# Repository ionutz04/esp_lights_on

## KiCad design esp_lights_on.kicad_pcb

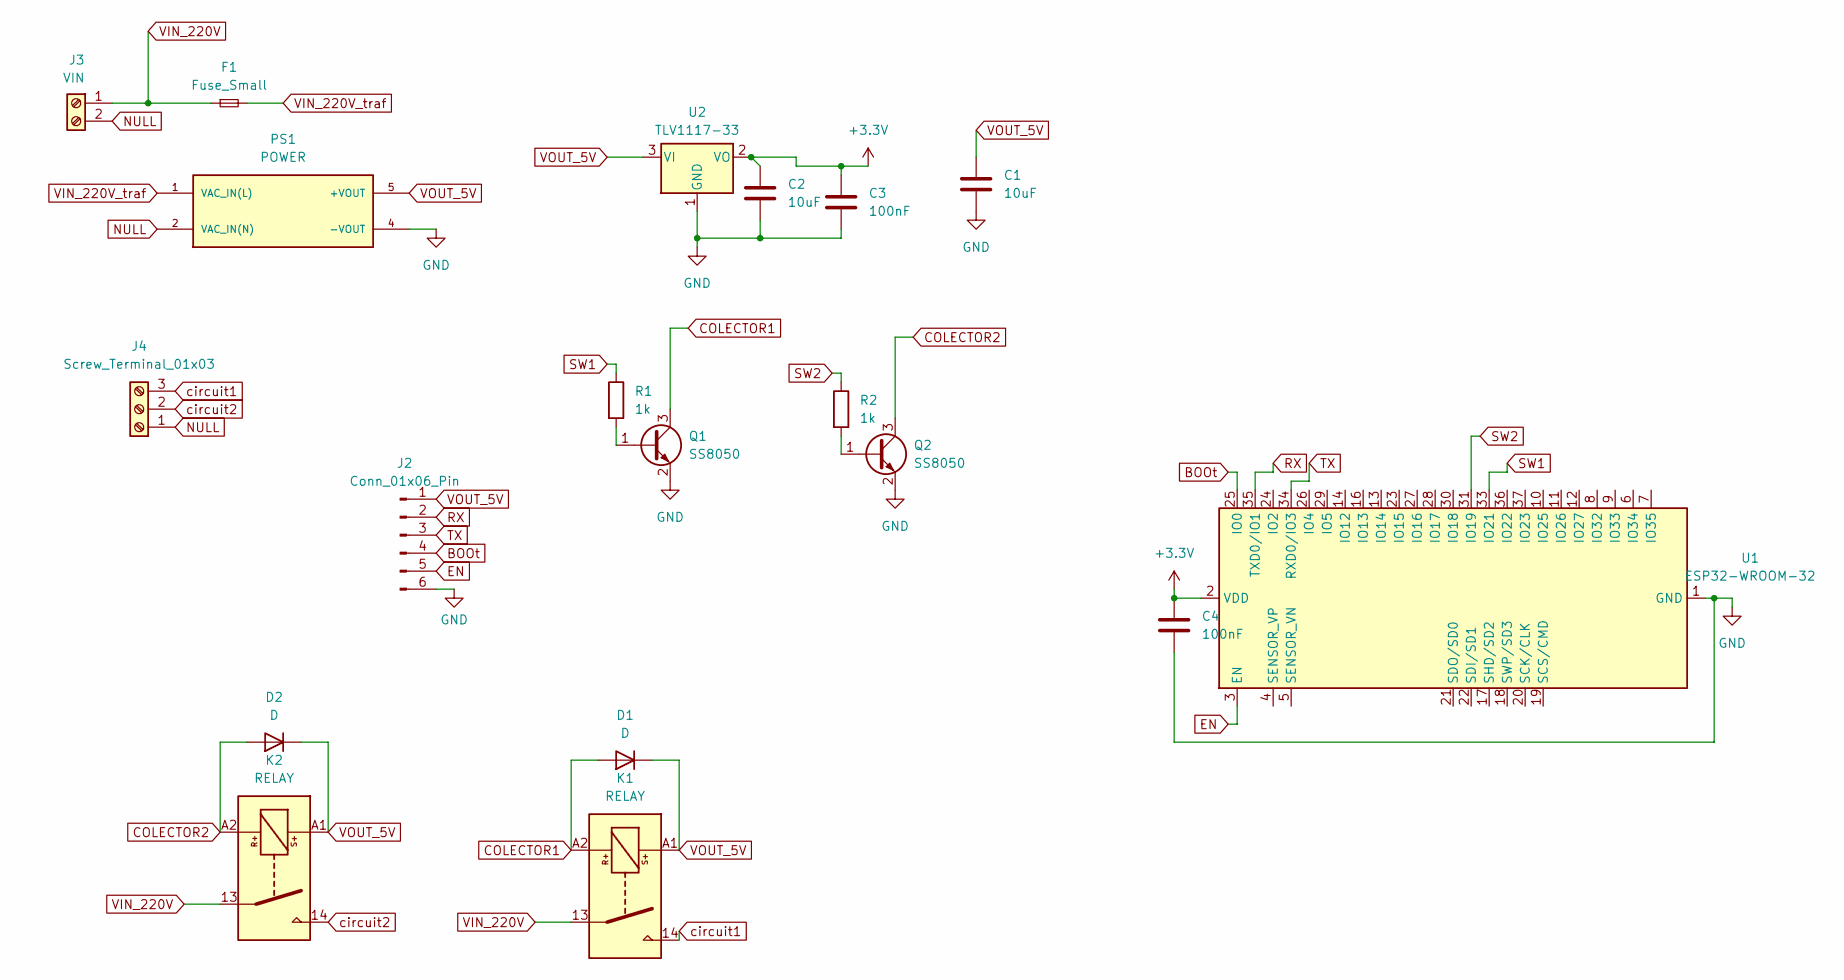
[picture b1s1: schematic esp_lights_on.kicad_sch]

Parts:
C1: 10uF; C_1210_3225Metric_Pad1.33x2.70mm_HandSolder
C2: 10uF; C_0805_2012Metric_Pad1.18x1.45mm_HandSolder
C3, C4: 100nF; C_0805_2012Metric_Pad1.18x1.45mm_HandSolder
D1, D2: D; D_SMA_Handsoldering
F1: Fuse_Small; Fuse_Schurter_UMZ250
J2: Conn_01x06_Pin; PinHeader_1x06_P2.54mm_Vertical
J3: VIN; TerminalBlock_Phoenix_MKDS-1,5-2-5.08_1x02_P5.08mm_Horizont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
J4: Screw_Terminal_01x03; TerminalBlock_Phoenix_MKDS-1,5-3-5.08_1x03_P5.08mm_Horizont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
K1, K2: RELAY; Relay_SPST_Panasonic_ADW11
PS1: POWER; CONV_RACM06E-12SK_277; PARTREV PRELIMINARY
Q1, Q2: SS8050; SOT-23-3
R1, R2: 1k; R_0805_2012Metric
U1: ESP32-WROOM-32
U2: TLV1117-33; SOT-223-3_TabPin2

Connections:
+3.3V: C2.1, C3.1, C4.1, U1.2 (VDD), U2.2 (VO)
BOOt: J2.4, U1.25 (IO0)
COLECTOR1: D1.2 (A), K1.A2, Q1.3 (C)
COLECTOR2: D2.2 (A), K2.A2, Q2.3 (C)
EN: J2.5, U1.3 (EN)
GND: C1.2, C2.2, C3.2, C4.2, J2.6, PS1.4 (-VOUT), Q1.2 (E), Q2.2 (E), U1.1 (GND), U1.15 (GND), U1.38 (GND), U1.39 (GND), U2.1 (GND)
NULL: J3.2, J4.1, PS1.2 (VAC_IN(N))
unnamed: Q1.1 (B), R1.2
unnamed: Q2.1 (B), R2.2
RX: J2.2, U1.35 (TXD0/IO1)
SW1: R1.1, U1.33 (IO21)
SW2: R2.1, U1.31 (IO19)
TX: J2.3, U1.34 (RXD0/IO3)
VIN_220V: F1.1, J3.1, K1.13, K2.13
VIN_220V_traf: F1.2, PS1.1 (VAC_IN(L))
VOUT_5V: C1.1, D1.1 (K), D2.1 (K), J2.1, K1.A1, K2.A1, PS1.5 (+VOUT), U2.3 (VI)
circuit1: J4.3, K1.14
circuit2: J4.2, K2.14

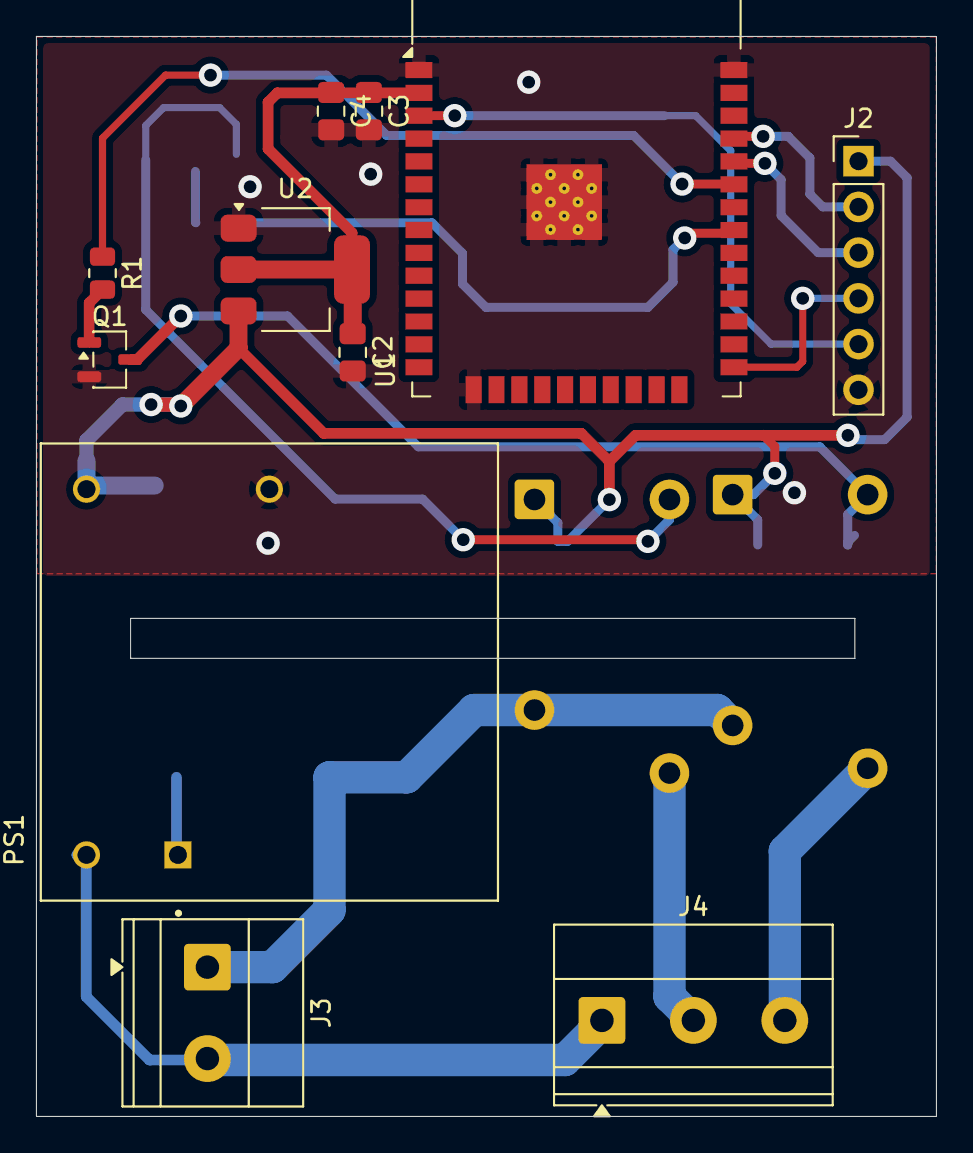
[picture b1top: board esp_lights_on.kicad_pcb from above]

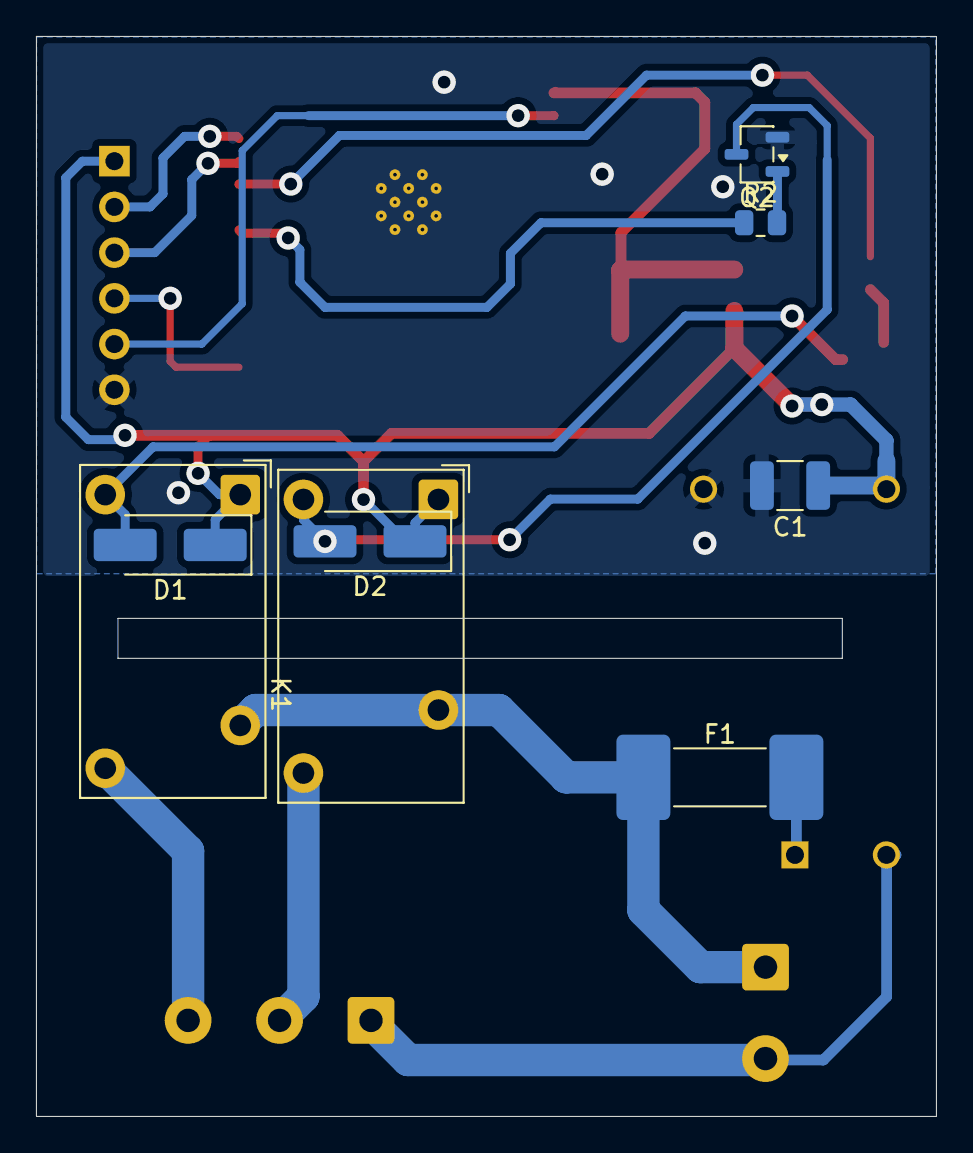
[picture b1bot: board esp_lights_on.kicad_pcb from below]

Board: 2 copper layers, 50.0 x 60.0 mm, 19 parts (6 on the bottom side), 18 nets.

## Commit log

2026-06-19 init commit
2026-06-19 addition of readme
2026-06-19 addition of github_actions
2026-06-19 fixes over the github actions
2026-06-19 some commits
2026-06-19 chore: actualizare randare PCB [skip ci]
2026-06-22 commit non-verified
2026-06-22 modification by ovi
2026-06-22 some other updates unverified
2026-06-22 final commit
2026-06-22 fixes
2026-06-22 other fixes
2026-06-22 some other fixes
2026-06-23 modifications by ovi
